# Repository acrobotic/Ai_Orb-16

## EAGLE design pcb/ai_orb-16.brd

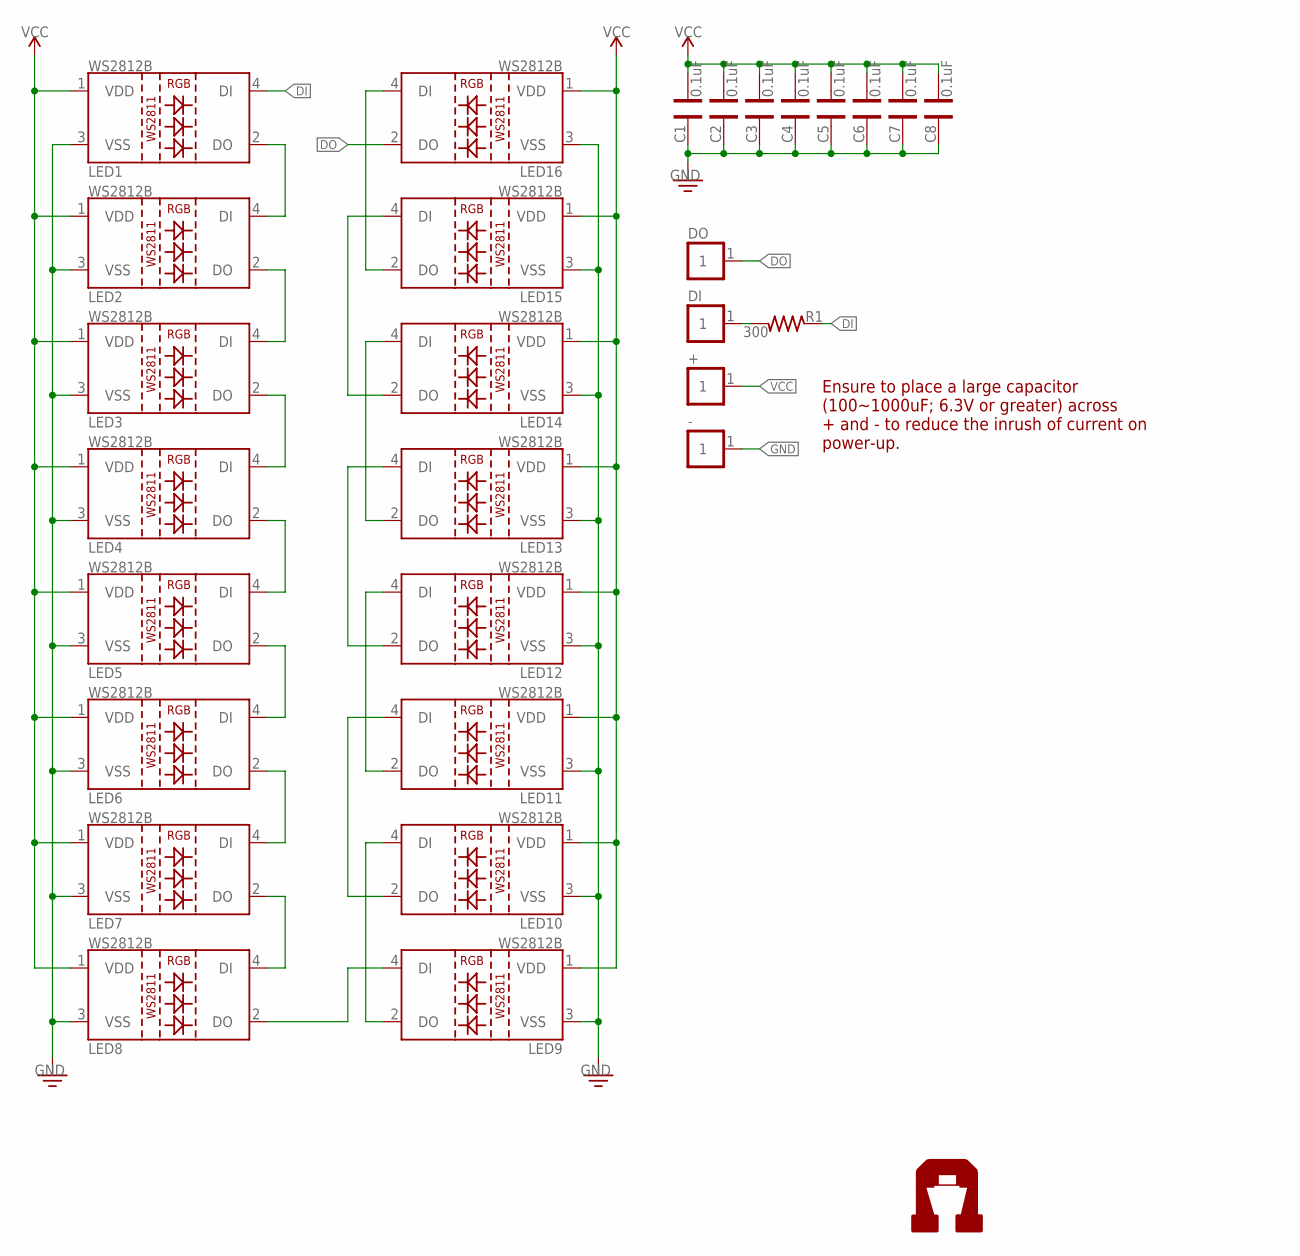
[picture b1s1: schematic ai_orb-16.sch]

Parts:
+: 1X01-SM
-: 1X01-SM
C1, C2, C3, C4, C5, C6, C7, C8: 0.1uF; CAP-0402
DI: 1X01-SM
DO: 1X01-SM
LED1, LED2, LED3, LED4, LED5, LED6, LED7, LED8, LED9, LED10, LED11, LED12, LED13, LED14, LED15, LED16: LED-WS2812B-SM
LOGO: AI-LOGOXS; AI-LOGO-XS
R1: 300; RES-0402

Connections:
DI: LED1.4 (DI), R1.1
DO: DO.1, LED16.2 (DO)
GND: -.1, C1.2, C2.2, C3.2, C4.2, C5.2, C6.2, C7.2, C8.2, LED1.3 (VSS), LED2.3 (VSS), LED3.3 (VSS), LED4.3 (VSS), LED5.3 (VSS), LED6.3 (VSS), LED7.3 (VSS), LED8.3 (VSS), LED9.3 (VSS), LED10.3 (VSS), LED11.3 (VSS), LED12.3 (VSS), LED13.3 (VSS), LED14.3 (VSS), LED15.3 (VSS), LED16.3 (VSS)
unnamed: LED1.2 (DO), LED2.4 (DI)
unnamed: LED2.2 (DO), LED3.4 (DI)
unnamed: DI.1, R1.2
unnamed: LED3.2 (DO), LED4.4 (DI)
unnamed: LED4.2 (DO), LED5.4 (DI)
unnamed: LED5.2 (DO), LED6.4 (DI)
unnamed: LED6.2 (DO), LED7.4 (DI)
unnamed: LED7.2 (DO), LED8.4 (DI)
unnamed: LED8.2 (DO), LED9.4 (DI)
unnamed: LED9.2 (DO), LED10.4 (DI)
unnamed: LED10.2 (DO), LED11.4 (DI)
unnamed: LED11.2 (DO), LED12.4 (DI)
unnamed: LED12.2 (DO), LED13.4 (DI)
unnamed: LED13.2 (DO), LED14.4 (DI)
unnamed: LED14.2 (DO), LED15.4 (DI)
unnamed: LED15.2 (DO), LED16.4 (DI)
VCC: +.1, C1.1, C2.1, C3.1, C4.1, C5.1, C6.1, C7.1, C8.1, LED1.1 (VDD), LED2.1 (VDD), LED3.1 (VDD), LED4.1 (VDD), LED5.1 (VDD), LED6.1 (VDD), LED7.1 (VDD), LED8.1 (VDD), LED9.1 (VDD), LED10.1 (VDD), LED11.1 (VDD), LED12.1 (VDD), LED13.1 (VDD), LED14.1 (VDD), LED15.1 (VDD), LED16.1 (VDD)

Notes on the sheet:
Ensure to place a large capacitor (100~1000uF; 6.3V or greater) across + and - to reduce the inrush of current on power-up.

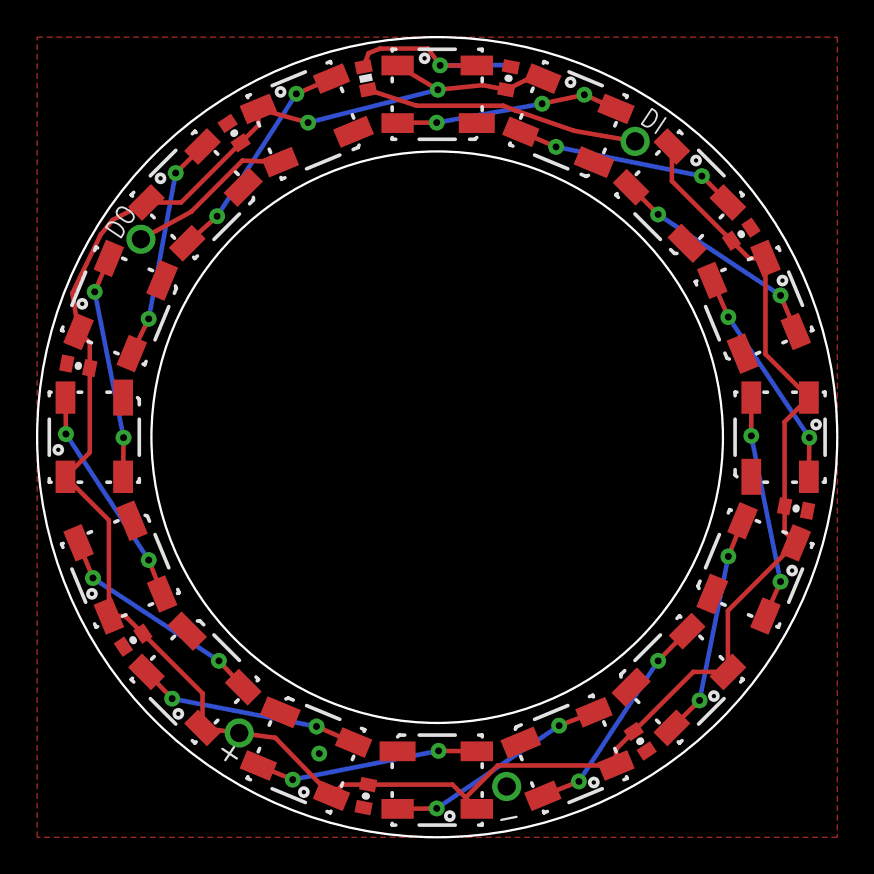
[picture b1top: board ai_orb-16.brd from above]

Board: 2 copper layers, 44.5 x 44.5 mm, 30 parts (1 on the bottom side), 20 nets.

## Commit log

2014-09-01 routed
2014-09-02 done w version 1.0
2014-09-02 minor change to silkscreen
2014-10-21 ready for manufacturing
2014-10-26 updating name
